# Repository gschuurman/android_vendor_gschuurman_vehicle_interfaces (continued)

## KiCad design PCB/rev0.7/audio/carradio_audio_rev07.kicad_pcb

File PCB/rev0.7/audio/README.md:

# Audio module rev 0.7: 2x PCM5102A + car mic input

2026-11-02. Plugs into the rev 0.6 main board exactly like the rev 0.4 audio module (same 41 x 36.5 mm outline, same J24 position, same standoff hole). Not pushed to any repo yet.

## What changed from rev 0.4
- **DAC side unchanged.** U8-U11 and their parts keep rev 0.4's copper on the top side, so the bit that already works stays the same.
- **New mic input on the underside**: a 3-pin JST XH socket J201 (on the top side) goes to a 3.5 mm stereo panel jack. Then electret bias (2.2k from a filtered 4.9 V), ESD diode, a 2-stage TLV9062 preamp (42 dB, or 33.5 dB with JP201 bridged), and a PCM1808 24-bit ADC.
- **Uses the two spare J24 lines** (checked against the rev 0.6 main-board netlist): pin 8 = VIM3 pin 30 (TDM-B MCLK, 256 fs into the ADC), pin 11 = VIM3 pin 35 (ADC data back to the VIM3, TDM-B lane 3). These are the pins the road-ready software patches already use, so the software doesn't change.
- PCM1808 runs as a slave (MD0/MD1 low), I2S 24-bit (FMT low), with BCK/LRCK shared with the DACs. The mic signal goes to both ADC inputs, so the HAL can use either one.

## Jack wiring (J201, XH 2.50 mm)
| J201 pin | Jack contact | Signal |
|---|---|---|
| 1 | Tip | mic + bias |
| 2 | Ring | unused (JP202 open) |
| 3 | Sleeve | GND |

JST XH is the common "2.54 mm JST". Its real pitch is 2.50 mm, and standard XH plugs fit it. JP202 stays open, so a mono plug (ring shorted to sleeve) is safe. Only bridge it for a mic that wants bias on both tip and ring.

## Board check
- DRC (KiCad 10): 0 unconnected, 0 clearance or copper errors. Schematic parity: nets and footprints match. The only differences are LCSC/MPN fields, which are not copied onto the footprints.
- What's left is cosmetic: silkscreen overlaps (mostly the dense labels on the underside), tiny dangling track stubs that don't affect copper, and R207/R208 plus C208/C209 sitting with courtyards touching (0.35 mm pad gap, so solder those carefully).
- 2 layers, 0.15 mm minimum track and gap, 0.3 mm vias.

## Ordering the PCB (JLCPCB)
Upload `carradio_audio_rev07_gerbers.zip` and keep the defaults: 2 layers, 1.6 mm, HASL lead-free, any colour, 5 pcs. The size comes in at 41 x 36.5 mm. Skip assembly, since you're soldering it yourself. The BOM/CPL files are there in case you change your mind.

## Parts to buy (LCSC, one board)
| Part | LCSC | Package | Qty per board | Refs | New in rev 0.7 |
|---|---|---|---|---|---|
| LP5907MFX-3.3 | C5370990 | SOT-23-5 | 2 | U8, U9 |  |
| 1uF | C77386 | C 0603 1608Metric | 9 | C18, C19, C20, C21, C24, C34, C205, C212, C213 | partly |
| PCM5102APWR | C107671 | TSSOP-20 4.4x6.5mm P0.65mm | 2 | U10, U11 |  |
| 2.2uF | C23630 | C 0603 1608Metric | 6 | C22, C23, C32, C33, C209, C211 | partly |
| 100nF | C14663 | C 0603 1608Metric | 11 | C25, C26, C27, C35, C36, C37, C203, C207, C215, C216, C217 | partly |
| 10uF | C15850 | C 0805 2012Metric | 9 | C28, C29, C38, C39, C202, C204, C206, C214, C218 | partly |
| 470Ω | C23179 | R 0603 1608Metric | 4 | R48, R49, R50, R51 |  |
| 2.2nF C0G | C28260 | C 0805 2012Metric | 4 | C30, C31, C40, C41 |  |
| Main board plug | C5116480 | PinHeader 2x10 P2.54mm Vertical | 1 | J24 |  |
| MIC (to 3.5 mm jack) | C144394 | JST XH B3B-XH-A 1x03 P2.50mm Vertical | 1 | J201 | yes |
| PESD5V0S1BA | C2827694 | D SOD-323 HandSoldering | 1 | D201 | yes |
| 1nF | C1588 | C 0603 1608Metric | 3 | C201, C208, C210 | yes |
| 10Ω | C22859 | R 0603 1608Metric | 1 | R201 | yes |
| 1k | C21190 | R 0603 1608Metric | 3 | R202, R208, R210 | yes |
| 2.2k | C4190 | R 0603 1608Metric | 1 | R203 | yes |
| 100k | C25803 | R 0603 1608Metric | 1 | R204 | yes |
| 10k | C25804 | R 0603 1608Metric | 4 | R205, R206, R207, R209 | yes |
| TLV9062IDR | C398355 | SOIC-8 3.9x4.9mm P1.27mm | 1 | U201 | yes |
| 4.7k | C23162 | R 0603 1608Metric | 1 | R211 | yes |
| PCM1808PWR | C55513 | TSSOP-14 4.4x5mm P0.65mm | 1 | U202 | yes |
| 33Ω | C23140 | R 0603 1608Metric | 1 | R212 | yes |

LCSC sells passives in strips of 50-100, so one order covers several boards. Every number above was checked on LCSC/JLCPCB today. J201's number was C144394 (the 3-pin part), not C144395 (that's the 4-pin).

**Also buy (no LCSC number given, any equivalent works):**
- A 3.5 mm stereo panel-mount jack (for example a PJ-392 style).
- A JST XH 3-pin housing (XHP-3) with SXH-001T-P0.6 crimps, or a pre-crimped XH 3-pin pigtail, which is easier.
- You already have the mic.

## Soldering order
1. Underside first, before J24 is in: U202 (PCM1808, TSSOP, 0.65 mm pitch, so flux and drag-solder), U201, then the 0603/0805 parts, D201.
2. Top side: U10/U11 (check PCM5102A pin 18/19 for a bridge, as on rev 0.6), U8/U9, the rest of the passives.
3. J24 (bottom) and J201 (top) last.

## Bench checks
- With the module powered, VIM3_5V is about 5 V, +5V_MIC about 4.9 V, and +3V3_DAC_A/D are 3.3 V.
- U202 pin 1 (VREF) reads about 2.45 V, and VMID (C206) about 2.45 V.
- With the mic plugged in, the tip sits at about 2-3 V. Without the mic it reads close to +5V_MIC.
- In Android or Linux: `arecord` on the mic capture device while you speak. If it clips, bridge JP201.

## Files
- `carradio_audio_rev07.kicad_sch / .kicad_pcb / .kicad_pro`: KiCad 10 project (open the .kicad_pro).
- `carradio_audio_rev07_schematic.pdf`, `render_top.png`, `render_bottom.png`
- `carradio_audio_rev07_bom.csv` (full BOM with notes), `carradio_audio_rev07_gerbers.zip`, `jlc_bom.csv` / `jlc_cpl.csv`

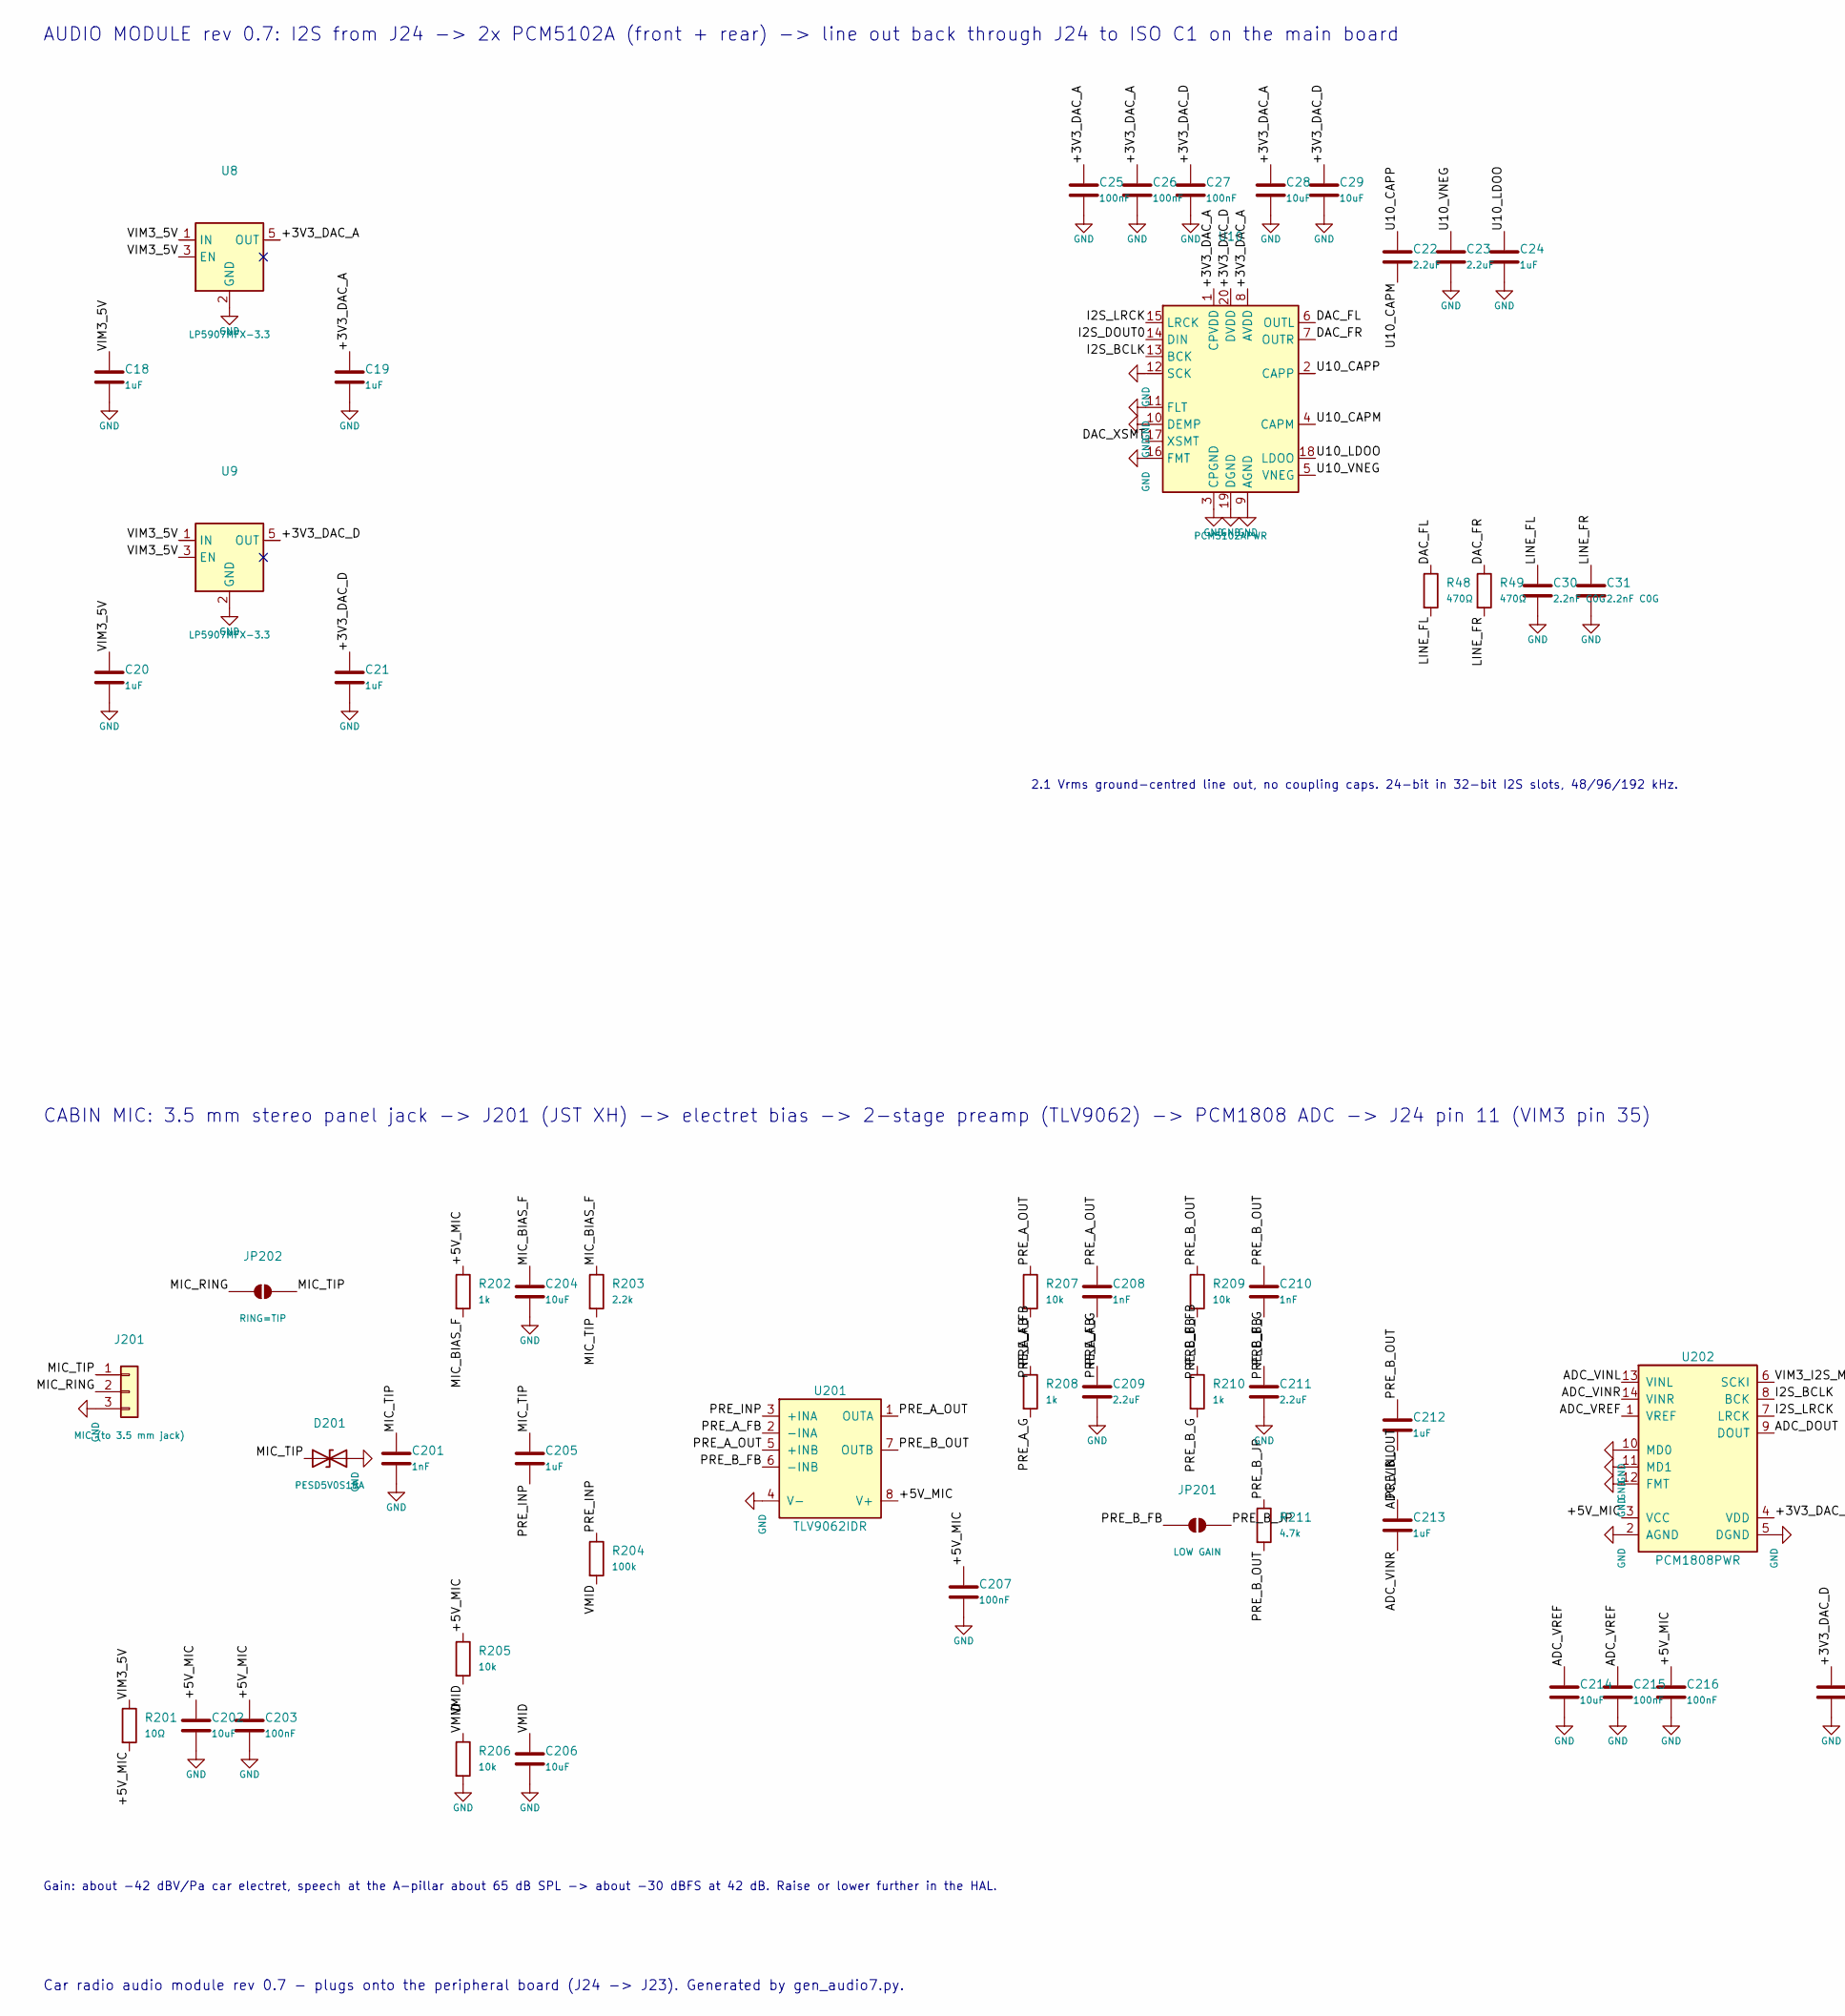
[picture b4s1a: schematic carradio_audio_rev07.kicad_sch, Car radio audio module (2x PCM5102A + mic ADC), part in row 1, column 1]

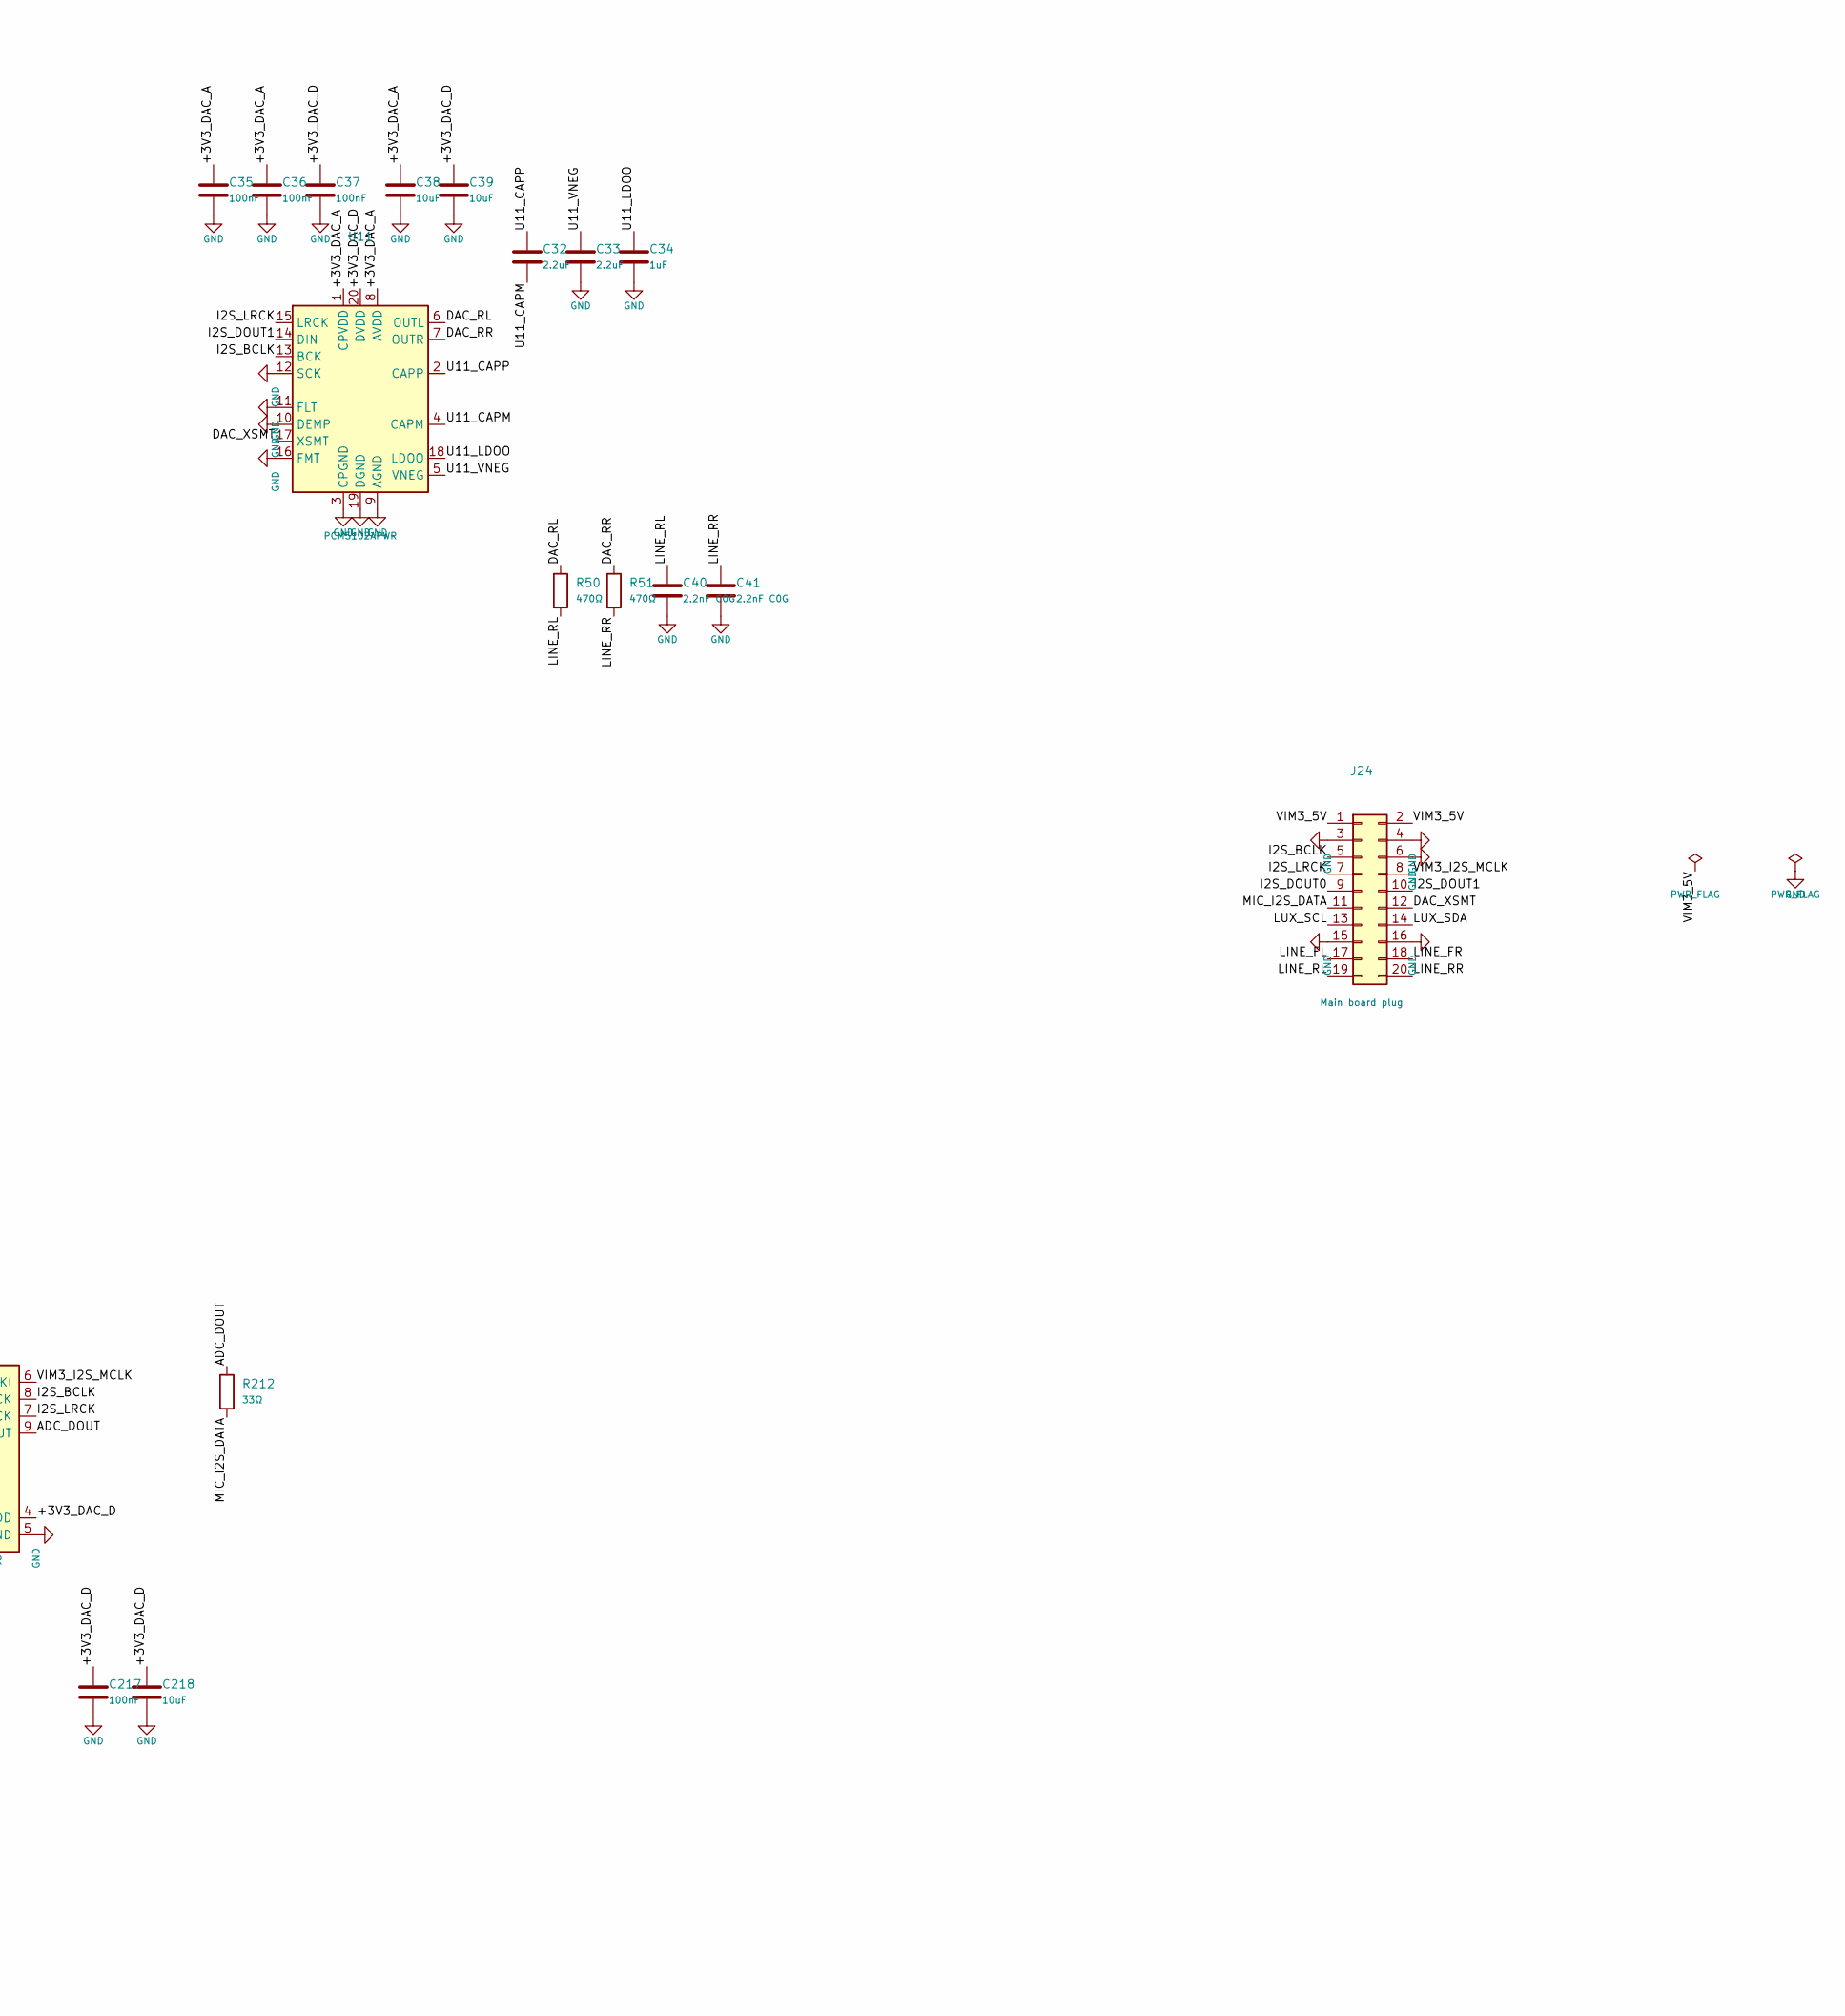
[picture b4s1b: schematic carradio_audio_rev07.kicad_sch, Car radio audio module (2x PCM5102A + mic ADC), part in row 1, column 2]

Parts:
C18, C19, C20, C21, C24, C34, C205, C212, C213: 1uF; C_0603_1608Metric; MPN 0603 1uF 50V X5R (Murata GRM188R61H105K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; LCSC C77386
C22, C23, C32, C33, C209, C211: 2.2uF; C_0603_1608Metric; MPN 0603 2.2uF 16V X5R; LCSC C23630
C25, C26, C27, C35, C36, C37, C203, C207, C215, C216, C217: 100nF; C_0603_1608Metric; MPN 0603 100nF 50V X7R; LCSC C14663
C28, C29, C38, C39, C202, C204, C206, C214, C218: 10uF; C_0805_2012Metric; MPN 0805 10uF 25V X5R; LCSC C15850
C30, C31, C40, C41: 2.2nF C0G; C_0805_2012Metric; MPN 0805 2.2nF 50V C0G; LCSC C28260
C201, C208, C210: 1nF; C_0603_1608Metric; MPN Samsung CL10B102KB8NNNC 0603 1nF 50V X7R; LCSC C1588
D201: PESD5V0S1BA; D_SOD-323_HandSoldering; MPN PESD5V0S1BA 5V ESD diode SOD-323 (TECH 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; LCSC C2827694
J24: Main board plug; PinHeader_2x10_P2.54mm_Vertical; MPN ZHOURI 2.54-2*10 male pin header; LCSC C5116480
J201: MIC (to 3.5 mm jack); JST_XH_B3B-XH-A_1x03_P2.50mm_Vertical; MPN JST B3B-XH-A(LF)(SN), 3-pin XH header (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; LCSC C144394
JP201: LOW GAIN; SolderJumper-2_P1.3mm_Open_Pad1.0x1.5mm; MPN solder jumper (PCB only)
JP202: RING=TIP; SolderJumper-2_P1.3mm_Open_Pad1.0x1.5mm; MPN solder jumper (PCB only)
R48, R49, R50, R51: 470Ω; R_0603_1608Metric; MPN 0603 470 1%; LCSC C23179
R201: 10Ω; R_0603_1608Metric; MPN 0603 10 1%; LCSC C22859
R202, R208, R210: 1k; R_0603_1608Metric; MPN 0603 1k 1%; LCSC C21190
R203: 2.2k; R_0603_1608Metric; MPN 0603 2.2k 1% (UNI-ROYAL 0603WAF2201T5E); LCSC C4190
R204: 100k; R_0603_1608Metric; MPN 0603 100k 1%; LCSC C25803
R205, R206, R207, R209: 10k; R_0603_1608Metric; MPN 0603 10k 1%; LCSC C25804
R211: 4.7k; R_0603_1608Metric; MPN 0603 4.7k 1%; LCSC C23162
R212: 33Ω; R_0603_1608Metric; MPN 0603 33 1%; LCSC C23140
U8, U9: LP5907MFX-3.3; SOT-23-5; MPN TI LP5907MFX-3.3/NOPB 250mA LDO (TECH P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; LCSC C5370990
U10, U11: PCM5102APWR; TSSOP-20_4.4x6.5mm_P0.65mm; MPN TI PCM5102APWR 32-bit 384kHz stereo DAC; LCSC C107671
U201: TLV9062IDR; SOIC-8_3.9x4.9mm_P1.27mm; MPN TI TLV9062IDR dual RRIO op-amp, 10 MHz,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; LCSC C398355
U202: PCM1808PWR; TSSOP-14_4.4x5mm_P0.65mm; MPN TI PCM1808PWR 24-bit 96 kHz stereo ADC 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; LCSC C55513

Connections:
/+3V3_DAC_A: C19.1, C25.1, C26.1, C28.1, C35.1, C36.1, C38.1, U8.5 (OUT), U10.1 (CPVDD), U10.8 (AVDD), U11.1 (CPVDD), U11.8 (AVDD)
/+3V3_DAC_D: C21.1, C27.1, C29.1, C37.1, C39.1, C217.1, C218.1, U9.5 (OUT), U10.20 (DVDD), U11.20 (DVDD), U202.4 (VDD)
/+5V_MIC: C202.1, C203.1, C207.1, C216.1, R201.2, R202.1, R205.1, U201.8 (V+), U202.3 (VCC)
/ADC_DOUT: R212.1, U202.9 (DOUT)
/ADC_VINL: C212.2, U202.13 (VINL)
/ADC_VINR: C213.2, U202.14 (VINR)
/ADC_VREF: C214.1, C215.1, U202.1 (VREF)
/DAC_FL: R48.1, U10.6 (OUTL)
/DAC_FR: R49.1, U10.7 (OUTR)
/DAC_RL: R50.1, U11.6 (OUTL)
/DAC_RR: R51.1, U11.7 (OUTR)
/DAC_XSMT: J24.12, U10.17 (XSMT), U11.17 (XSMT)
/I2S_BCLK: J24.5, U10.13 (BCK), U11.13 (BCK), U202.8 (BCK)
/I2S_DOUT0: J24.9, U10.14 (DIN)
/I2S_DOUT1: J24.10, U11.14 (DIN)
/I2S_LRCK: J24.7, U10.15 (LRCK), U11.15 (LRCK), U202.7 (LRCK)
/LINE_FL: C30.1, J24.17, R48.2
/LINE_FR: C31.1, J24.18, R49.2
/LINE_RL: C40.1, J24.19, R50.2
/LINE_RR: C41.1, J24.20, R51.2
/LUX_SCL: J24.13
/LUX_SDA: J24.14
/MIC_BIAS_F: C204.1, R202.2, R203.1
/MIC_I2S_DATA: J24.11, R212.2
/MIC_RING: J201.2, JP202.1 (A)
/MIC_TIP: C201.1, C205.1, D201.1 (A1), J201.1, JP202.2 (B), R203.2
/PRE_A_FB: C208.2, R207.2, R208.1, U201.2 (-INA)
/PRE_A_G: C209.1, R208.2
/PRE_A_OUT: C208.1, R207.1, U201.1 (OUTA), U201.5 (+INB)
/PRE_B_FB: C210.2, JP201.1 (A), R209.2, R210.1, U201.6 (-INB)
/PRE_B_G: C211.1, R210.2
/PRE_B_JP: JP201.2 (B), R211.1
/PRE_B_OUT: C210.1, C212.1, C213.1, R209.1, R211.2, U201.7 (OUTB)
/PRE_INP: C205.2, R204.1, U201.3 (+INA)
/U10_CAPM: C22.2, U10.4 (CAPM)
/U10_CAPP: C22.1, U10.2 (CAPP)
/U10_LDOO: C24.1, U10.18 (LDOO)
/U10_VNEG: C23.1, U10.5 (VNEG)
/U11_CAPM: C32.2, U11.4 (CAPM)
/U11_CAPP: C32.1, U11.2 (CAPP)
/U11_LDOO: C34.1, U11.18 (LDOO)
/U11_VNEG: C33.1, U11.5 (VNEG)
/VIM3_5V: C18.1, C20.1, J24.1, J24.2, R201.1, U8.1 (IN), U8.3 (EN), U9.1 (IN), U9.3 (EN)
/VIM3_I2S_MCLK: J24.8, U202.6 (SCKI)
/VMID: C206.1, R204.2, R205.2, R206.1
GND: C18.2, C19.2, C20.2, C21.2, C23.2, C24.2, C25.2, C26.2, C27.2, C28.2, C29.2, C30.2, C31.2, C33.2, C34.2, C35.2, C36.2, C37.2, C38.2, C39.2, C40.2, C41.2, C201.2, C202.2, C203.2, C204.2, C206.2, C207.2, C209.2, C211.2, C214.2, C215.2, C216.2, C217.2, C218.2, D201.2 (A2), J24.3, J24.4, J24.6, J24.15, J24.16, J201.3, R206.2, U8.2 (GND), U9.2 (GND), U10.3 (CPGND), U10.9 (AGND), U10.10 (DEMP), U10.11 (FLT), U10.12 (SCK), U10.16 (FMT), U10.19 (DGND), U11.3 (CPGND), U11.9 (AGND), U11.10 (DEMP), U11.11 (FLT), U11.12 (SCK), U11.16 (FMT), U11.19 (DGND), U201.4 (V-), U202.2 (AGND), U202.5 (DGND), U202.10 (MD0), U202.11 (MD1), U202.12 (FMT); also elsewhere on the board

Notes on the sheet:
AUDIO MODULE rev 0.7: I2S from J24 -> 2x PCM5102A (front + rear) -> line out back through J24 to ISO C1 on the main board
2.1 Vrms ground-centred line out, no coupling caps. 24-bit in 32-bit I2S slots, 48/96/192 kHz.
CABIN MIC: 3.5 mm stereo panel jack -> J201 (JST XH) -> electret bias -> 2-stage preamp (TLV9062) -> PCM1808 ADC -> J24 pin 11 (VIM3 pin 35)
Gain: about -42 dBV/Pa car electret, speech at the A-pillar about 65 dB SPL -> about -30 dBFS at 42 dB. Raise or lower further in the HAL.
Car radio audio module rev 0.7 - plugs onto the peripheral board (J24 -> J23). Generated by gen_audio7.py.

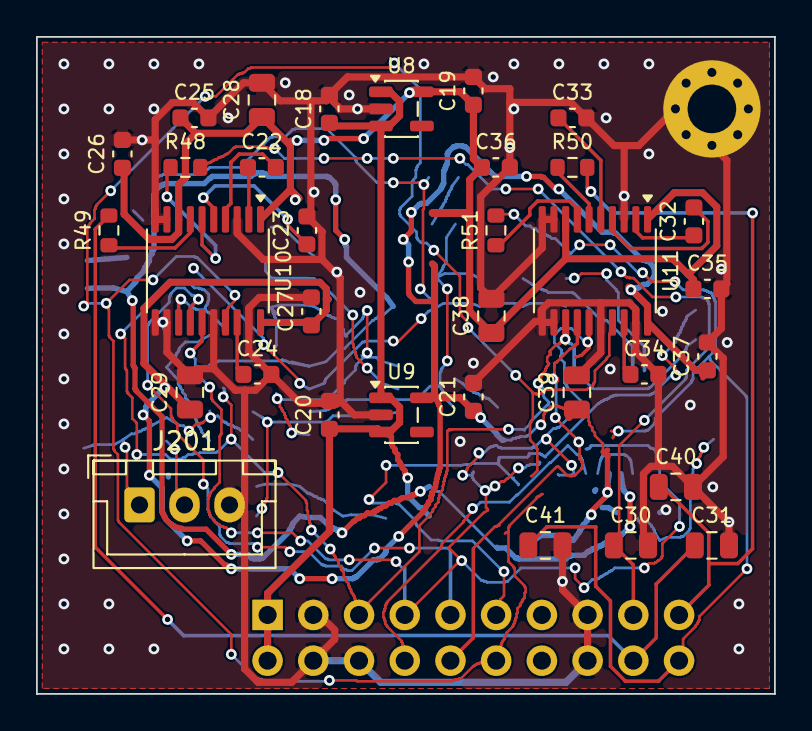
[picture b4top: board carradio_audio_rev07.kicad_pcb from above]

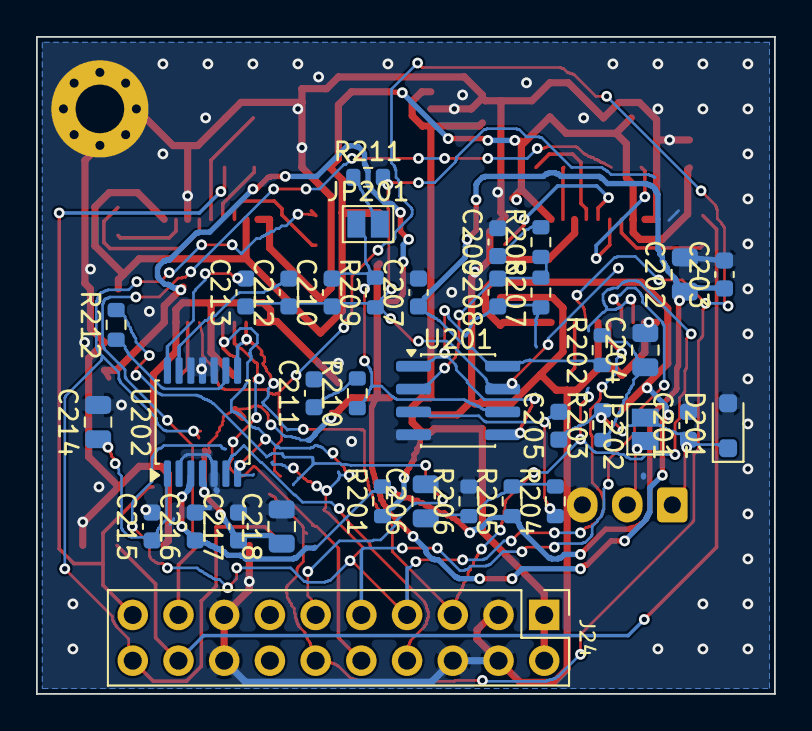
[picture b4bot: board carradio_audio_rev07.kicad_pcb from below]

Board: 2 copper layers, 41.0 x 36.5 mm, 70 parts (36 on the bottom side), 44 nets.

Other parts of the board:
H1: M2.5 standoff; MountingHole_2.7mm_M2.5_Pad_Via

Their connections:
GND: H1.1; also elsewhere on the board

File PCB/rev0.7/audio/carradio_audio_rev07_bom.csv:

Designator,Value,Description / MPN,LCSC,Footprint (KiCad name),Fit,Note
U8,LP5907MFX-3.3,TI LP5907MFX-3.3/NOPB 250mA LDO (TECH PUBLIC TPLP5907MFX-3.3 clone; TI part out of stock at LCSC),C5370990,Package_TO_SOT_SMD:SOT-23-5,yes,DAC analog supply (AVDD + CPVDD)
C18,1uF,0603 1uF 50V X5R (Murata GRM188R61H105KAALD),C77386,Capacitor_SMD:C_0603_1608Metric,yes,
C19,1uF,0603 1uF 50V X5R (Murata GRM188R61H105KAALD),C77386,Capacitor_SMD:C_0603_1608Metric,yes,
U9,LP5907MFX-3.3,TI LP5907MFX-3.3/NOPB 250mA LDO (TECH PUBLIC TPLP5907MFX-3.3 clone; TI part out of stock at LCSC),C5370990,Package_TO_SOT_SMD:SOT-23-5,yes,"DAC + mic ADC digital supply (DVDD, PCM1808 VDD)"
C20,1uF,0603 1uF 50V X5R (Murata GRM188R61H105KAALD),C77386,Capacitor_SMD:C_0603_1608Metric,yes,
C21,1uF,0603 1uF 50V X5R (Murata GRM188R61H105KAALD),C77386,Capacitor_SMD:C_0603_1608Metric,yes,
U10,PCM5102APWR,TI PCM5102APWR 32-bit 384kHz stereo DAC,C107671,Package_SO:TSSOP-20_4.4x6.5mm_P0.65mm,yes,"Front L/R, TDM-B lane 0. SCK=GND (PLL from BCK), FMT=GND (I2S), FLT=GND (normal latency), DEMP=GND"
C22,2.2uF,0603 2.2uF 16V X5R,C23630,Capacitor_SMD:C_0603_1608Metric,yes,charge-pump flying cap
C23,2.2uF,0603 2.2uF 16V X5R,C23630,Capacitor_SMD:C_0603_1608Metric,yes,
C24,1uF,0603 1uF 50V X5R (Murata GRM188R61H105KAALD),C77386,Capacitor_SMD:C_0603_1608Metric,yes,"LDOO: pin 18, next to GND pin 19; check for a bridge after soldering"
C25,100nF,0603 100nF 50V X7R,C14663,Capacitor_SMD:C_0603_1608Metric,yes,at CPVDD
C26,100nF,0603 100nF 50V X7R,C14663,Capacitor_SMD:C_0603_1608Metric,yes,at AVDD
C27,100nF,0603 100nF 50V X7R,C14663,Capacitor_SMD:C_0603_1608Metric,yes,at DVDD
C28,10uF,0805 10uF 25V X5R,C15850,Capacitor_SMD:C_0805_2012Metric,yes,
C29,10uF,0805 10uF 25V X5R,C15850,Capacitor_SMD:C_0805_2012Metric,yes,
R48,470Ω,0603 470 1%,C23179,Resistor_SMD:R_0603_1608Metric,yes,output RC filter (datasheet)
R49,470Ω,0603 470 1%,C23179,Resistor_SMD:R_0603_1608Metric,yes,
C30,2.2nF C0G,0805 2.2nF 50V C0G,C28260,Capacitor_SMD:C_0805_2012Metric,yes,
C31,2.2nF C0G,0805 2.2nF 50V C0G,C28260,Capacitor_SMD:C_0805_2012Metric,yes,
U11,PCM5102APWR,TI PCM5102APWR 32-bit 384kHz stereo DAC,C107671,Package_SO:TSSOP-20_4.4x6.5mm_P0.65mm,yes,"Rear L/R, TDM-B lane 1. SCK=GND (PLL from BCK), FMT=GND (I2S), FLT=GND (normal latency), DEMP=GND"
C32,2.2uF,0603 2.2uF 16V X5R,C23630,Capacitor_SMD:C_0603_1608Metric,yes,charge-pump flying cap
C33,2.2uF,0603 2.2uF 16V X5R,C23630,Capacitor_SMD:C_0603_1608Metric,yes,
C34,1uF,0603 1uF 50V X5R (Murata GRM188R61H105KAALD),C77386,Capacitor_SMD:C_0603_1608Metric,yes,"LDOO: pin 18, next to GND pin 19; check for a bridge after soldering"
C35,100nF,0603 100nF 50V X7R,C14663,Capacitor_SMD:C_0603_1608Metric,yes,at CPVDD
C36,100nF,0603 100nF 50V X7R,C14663,Capacitor_SMD:C_0603_1608Metric,yes,at AVDD
C37,100nF,0603 100nF 50V X7R,C14663,Capacitor_SMD:C_0603_1608Metric,yes,at DVDD
C38,10uF,0805 10uF 25V X5R,C15850,Capacitor_SMD:C_0805_2012Metric,yes,
C39,10uF,0805 10uF 25V X5R,C15850,Capacitor_SMD:C_0805_2012Metric,yes,
R50,470Ω,0603 470 1%,C23179,Resistor_SMD:R_0603_1608Metric,yes,output RC filter (datasheet)
R51,470Ω,0603 470 1%,C23179,Resistor_SMD:R_0603_1608Metric,yes,
C40,2.2nF C0G,0805 2.2nF 50V C0G,C28260,Capacitor_SMD:C_0805_2012Metric,yes,
C41,2.2nF C0G,0805 2.2nF 50V C0G,C28260,Capacitor_SMD:C_0805_2012Metric,yes,
J24,Main board plug,ZHOURI 2.54-2*10 male pin header,C5116480,Connector_PinHeader_2.54mm:PinHeader_2x10_P2.54mm_Vertical,yes,"mates with J23 on the main board; fit on the bottom side. Pin 8 = VIM3 pin 30 (TDM-B MCLK), pin 11 = VIM3 pin 35 (GPIOH_5, TDM-B lane 3, main-board net VIM3_I2S_DOUT2) now carries the mic ADC data to the VIM3"
J201,MIC (to 3.5 mm jack),"JST B3B-XH-A(LF)(SN), 3-pin XH header (Mouser 306-B3B-XH-ALFSN)",C144394,Connector_JST:JST_XH_B3B-XH-A_1x03_P2.50mm_Vertical,yes,"cable to a 3.5 mm stereo panel jack: 1 = tip (mic + bias), 2 = ring, 3 = sleeve (GND)"
JP202,RING=TIP,solder jumper (PCB only),,Jumper:SolderJumper-2_P1.3mm_Open_Pad1.0x1.5mm,yes,"open by default: ring unused, so a mono plug (ring shorted to sleeve) is safe. Bridge only for a mic whose plug wants bias on tip and ring"
D201,PESD5V0S1BA,PESD5V0S1BA 5V ESD diode SOD-323 (TECH PUBLIC),C2827694,Diode_SMD:D_SOD-323_HandSoldering,yes,ESD clamp on the jack line
C201,1nF,Samsung CL10B102KB8NNNC 0603 1nF 50V X7R,C1588,Capacitor_SMD:C_0603_1608Metric,yes,RF (GSM buzz) filter at the jack line
R201,10Ω,0603 10 1%,C22859,Resistor_SMD:R_0603_1608Metric,yes,RC filter with C202/C203: quiet 4.9 V for the preamp and PCM1808 VCC
C202,10uF,0805 10uF 25V X5R,C15850,Capacitor_SMD:C_0805_2012Metric,yes,
C203,100nF,0603 100nF 50V X7R,C14663,Capacitor_SMD:C_0603_1608Metric,yes,
R202,1k,0603 1k 1%,C21190,Resistor_SMD:R_0603_1608Metric,yes,
C204,10uF,0805 10uF 25V X5R,C15850,Capacitor_SMD:C_0805_2012Metric,yes,"bias filter, 16 Hz"
R203,2.2k,0603 2.2k 1% (UNI-ROYAL 0603WAF2201T5E),C4190,Resistor_SMD:R_0603_1608Metric,yes,electret bias resistor (standard 2.2k plug-in-power load)
C205,1uF,0603 1uF 50V X5R (Murata GRM188R61H105KAALD),C77386,Capacitor_SMD:C_0603_1608Metric,yes,input coupling
R204,100k,0603 100k 1%,C25803,Resistor_SMD:R_0603_1608Metric,yes,
R205,10k,0603 10k 1%,C25804,Resistor_SMD:R_0603_1608Metric,yes,
R206,10k,0603 10k 1%,C25804,Resistor_SMD:R_0603_1608Metric,yes,
C206,10uF,0805 10uF 25V X5R,C15850,Capacitor_SMD:C_0805_2012Metric,yes,mid-rail reference 2.45 V
U201,TLV9062IDR,"TI TLV9062IDR dual RRIO op-amp, 10 MHz, 1.8-5.5 V (Mouser 595-TLV9062IDR)",C398355,Package_SO:SOIC-8_3.9x4.9mm_P1.27mm,yes,"stage A 21 dB, stage B 21 dB (JP201 bridged: 12.5 dB); 1 Hz-10 kHz voice band"
C207,100nF,0603 100nF 50V X7R,C14663,Capacitor_SMD:C_0603_1608Metric,yes,at U201 pin 8
R207,10k,0603 10k 1%,C25804,Resistor_SMD:R_0603_1608Metric,yes,stage A feedback
C208,1nF,Samsung CL10B102KB8NNNC 0603 1nF 50V X7R,C1588,Capacitor_SMD:C_0603_1608Metric,yes,"stage A low-pass, 16 kHz"
R208,1k,0603 1k 1%,C21190,Resistor_SMD:R_0603_1608Metric,yes,
C209,2.2uF,0603 2.2uF 16V X5R,C23630,Capacitor_SMD:C_0603_1608Metric,yes,AC gain only; 72 Hz low cut against road rumble
R209,10k,0603 10k 1%,C25804,Resistor_SMD:R_0603_1608Metric,yes,stage B feedback
C210,1nF,Samsung CL10B102KB8NNNC 0603 1nF 50V X7R,C1588,Capacitor_SMD:C_0603_1608Metric,yes,"stage B low-pass, 16 kHz"
R210,1k,0603 1k 1%,C21190,Resistor_SMD:R_0603_1608Metric,yes,
C211,2.2uF,0603 2.2uF 16V X5R,C23630,Capacitor_SMD:C_0603_1608Metric,yes,AC gain only; 72 Hz low cut
JP201,LOW GAIN,solder jumper (PCB only),,Jumper:SolderJumper-2_P1.3mm_Open_Pad1.0x1.5mm,yes,"open = 42 dB total (default), bridged = 33.5 dB (puts R211 across R209) for a hot mic or a loud cabin"
R211,4.7k,0603 4.7k 1%,C23162,Resistor_SMD:R_0603_1608Metric,yes,
C212,1uF,0603 1uF 50V X5R (Murata GRM188R61H105KAALD),C77386,Capacitor_SMD:C_0603_1608Metric,yes,"ADC input coupling (60k input, 2.7 Hz)"
C213,1uF,0603 1uF 50V X5R (Murata GRM188R61H105KAALD),C77386,Capacitor_SMD:C_0603_1608Metric,yes,same signal on the right input; the HAL may use either
U202,PCM1808PWR,TI PCM1808PWR 24-bit 96 kHz stereo ADC (Mouser 595-PCM1808PWR),C55513,Package_SO:TSSOP-14_4.4x5mm_P0.65mm,yes,"slave mode (MD1/MD0 low), I2S (FMT low), SCKI = 256 fs from VIM3 pin 30, BCK 64 fs; pinout from TI SLES177B"
C214,10uF,0805 10uF 25V X5R,C15850,Capacitor_SMD:C_0805_2012Metric,yes,VREF decoupling (datasheet: 0.1 uF + 10 uF)
C215,100nF,0603 100nF 50V X7R,C14663,Capacitor_SMD:C_0603_1608Metric,yes,
C216,100nF,0603 100nF 50V X7R,C14663,Capacitor_SMD:C_0603_1608Metric,yes,at U202 VCC
C217,100nF,0603 100nF 50V X7R,C14663,Capacitor_SMD:C_0603_1608Metric,yes,at U202 VDD
C218,10uF,0805 10uF 25V X5R,C15850,Capacitor_SMD:C_0805_2012Metric,yes,at U202 VDD
R212,33Ω,0603 33 1%,C23140,Resistor_SMD:R_0603_1608Metric,yes,source termination for the data line to the VIM3
